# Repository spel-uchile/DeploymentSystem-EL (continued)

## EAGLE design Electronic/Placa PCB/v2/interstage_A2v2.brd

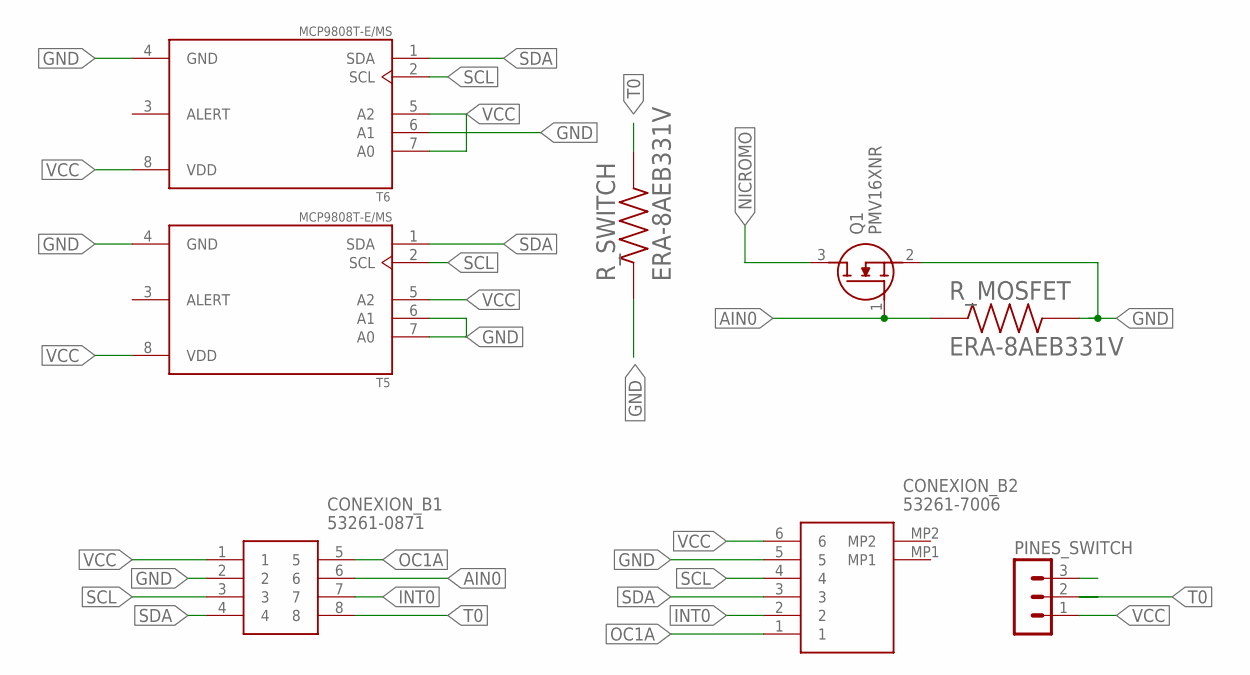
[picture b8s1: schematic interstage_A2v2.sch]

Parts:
CONEXION_B1: 53261-0871
CONEXION_B2: 53261-7006; 532617006
PINES_SWITCH: MA03-1
Q1: PMV16XNR; SOT95P230X110-3N
R_MOSFET: ERA-8AEB331V; RESC3216X70N
R_SWITCH: ERA-8AEB331V; RESC3216X70N
T5, T6: MCP9808T-E/MS; SOP65P490X110-8N

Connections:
AIN0: CONEXION_B1.6, Q1.1 (G), R_MOSFET.1
GND: CONEXION_B1.2, CONEXION_B2.5, Q1.2 (S), R_MOSFET.2, R_SWITCH.1, T5.4 (GND), T5.6 (A1), T5.7 (A0), T6.4 (GND), T6.6 (A1)
INT0: CONEXION_B1.7, CONEXION_B2.2
NICROMO: Q1.3 (D)
OC1A: CONEXION_B1.5, CONEXION_B2.1
SCL: CONEXION_B1.3, CONEXION_B2.4, T5.2 (SCL), T6.2 (SCL)
SDA: CONEXION_B1.4, CONEXION_B2.3, T5.1 (SDA), T6.1 (SDA)
T0: CONEXION_B1.8, PINES_SWITCH.2, R_SWITCH.2
VCC: CONEXION_B1.1, CONEXION_B2.6, PINES_SWITCH.1, T5.5 (A2), T5.8 (VDD), T6.5 (A2), T6.7 (A0), T6.8 (VDD)

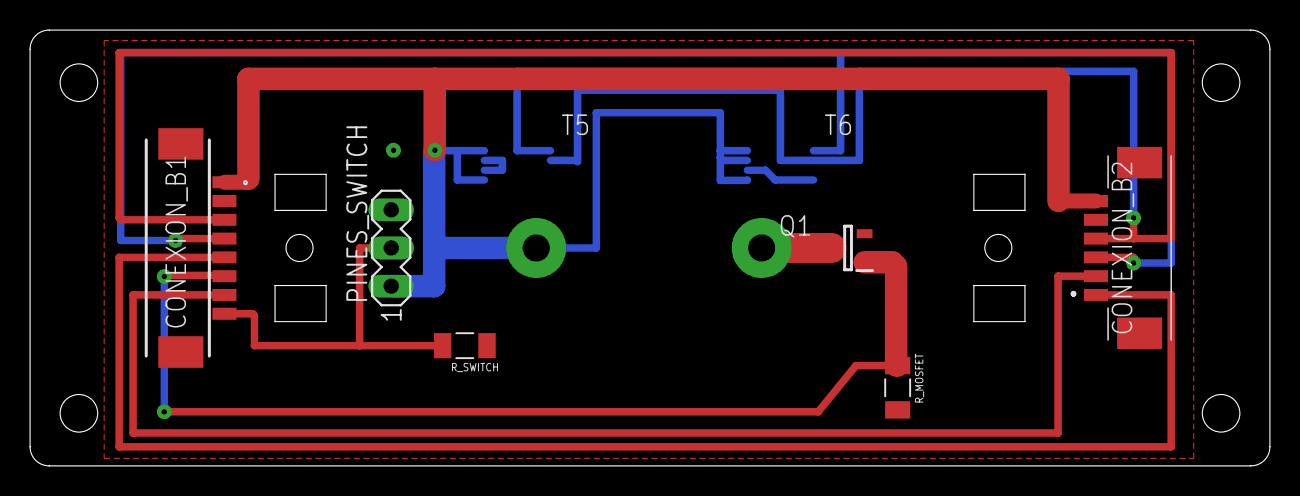
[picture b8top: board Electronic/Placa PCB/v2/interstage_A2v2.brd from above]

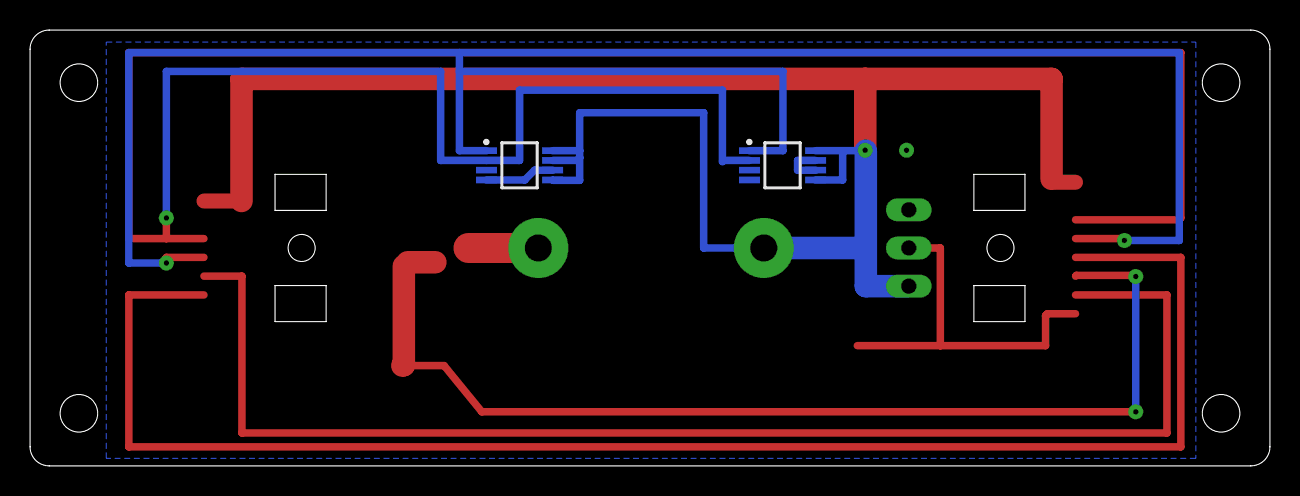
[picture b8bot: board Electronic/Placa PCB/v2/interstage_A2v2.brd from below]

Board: 2 copper layers, 82.5 x 29.0 mm, 8 parts (2 on the bottom side), 8 nets.

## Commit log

2020-03-25 Initial files
2020-04-06 DXF files
2020-04-13 IS version with hole
2020-04-13 HoleIS
2020-04-15 DXF Files modificados
2020-05-14 Presentación
2020-05-18 Placas PCB
2020-05-18 Placas PCB
2020-05-19 Soportes para paneles
2020-05-24 Ensamblaje placa
2020-06-16 Avance
2020-06-30 Mini placas
2020-07-11 Presentacion II
2020-08-17 gerbers
2020-08-17 Gerber V3
2020-08-22 Actualización
